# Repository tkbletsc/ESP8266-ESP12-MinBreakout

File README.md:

# ESP8266-ESP12-MinBreakout
Minimal breakout board for the ESP8266 model ESP12 board

A breakout board for the ESP8266 model ESP12 board, but with a twist. The down-facing header pins are installed with very little protrusion on the top, then some insulation is added (electrical tape), then the ESP12 is SMT soldered on top. This makes this breakout far smaller than the existing ones, and much more breadboard friendly.

Comes in through-hole and SMT flavors. The through-hole flavor rev1 has been successfully fabbed and populated and works perfectly.

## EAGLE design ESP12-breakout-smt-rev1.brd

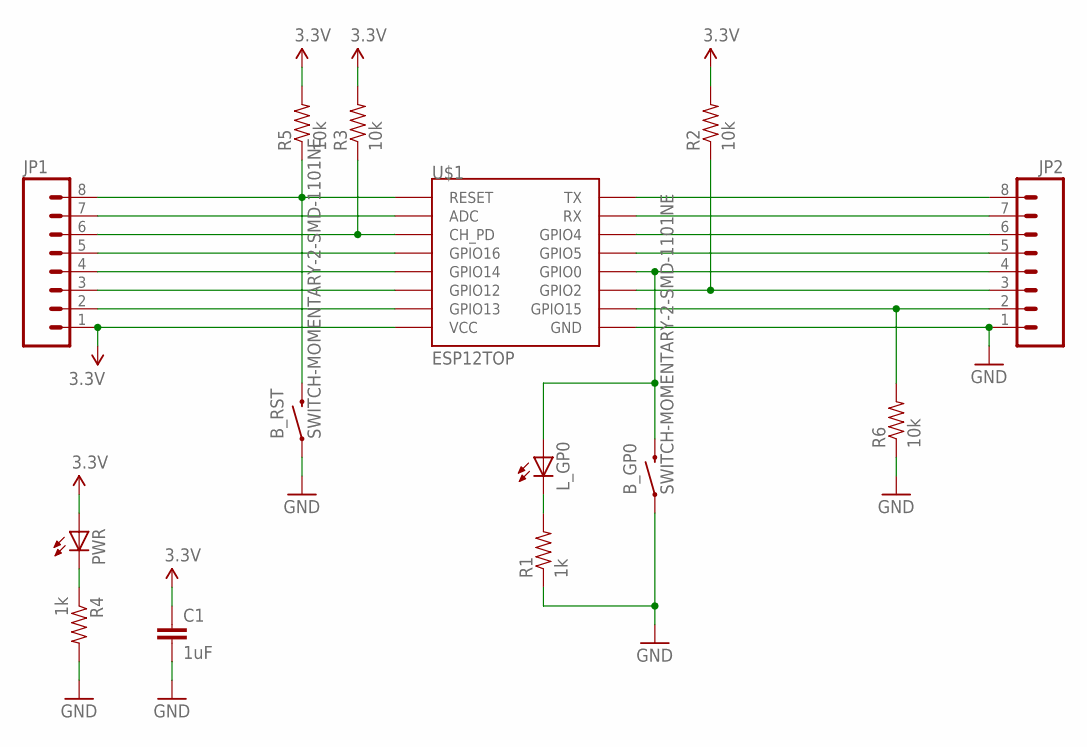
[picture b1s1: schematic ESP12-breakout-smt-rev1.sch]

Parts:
B_GP0: SWITCH-MOMENTARY-2-SMD-1101NE; TACTILE-SWITCH-1101NE
B_RST: SWITCH-MOMENTARY-2-SMD-1101NE; TACTILE-SWITCH-1101NE
C1: 1uF; 0805
JP1, JP2: M08; 1X08_PIN1_NO_SILK
L_GP0: LEDCHIPLED_0805; CHIPLED_0805
PWR: LEDCHIPLED_0805; CHIPLED_0805
R1, R4: 1k; 0603-RES
R2, R3, R5, R6: 10k; 0603-RES
U$1: ESP12TOP

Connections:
3.3V: C1.1, JP1.1, PWR.A, R2.2, R3.2, R5.2, U$1.VCC
GND: B_GP0.1, B_RST.1, C1.2, JP2.1, R1.1, R4.2, R6.1, U$1.GND
unnamed: L_GP0.C, R1.2
unnamed: JP1.2, U$1.GPIO13
unnamed: JP1.3, U$1.GPIO12
unnamed: JP1.4, U$1.GPIO14
unnamed: JP1.5, U$1.GPIO16
unnamed: JP1.6, R3.1, U$1.CH_PD
unnamed: JP1.7, U$1.ADC
unnamed: B_RST.2, JP1.8, R5.1, U$1.RESET
unnamed: PWR.C, R4.1
unnamed: JP2.2, R6.2, U$1.GPIO15
unnamed: JP2.3, R2.1, U$1.GPIO2
unnamed: B_GP0.2, JP2.4, L_GP0.A, U$1.GPIO0
unnamed: JP2.5, U$1.GPIO5
unnamed: JP2.6, U$1.GPIO4
unnamed: JP2.7, U$1.RXD (RX)
unnamed: JP2.8, U$1.TXD (TX)

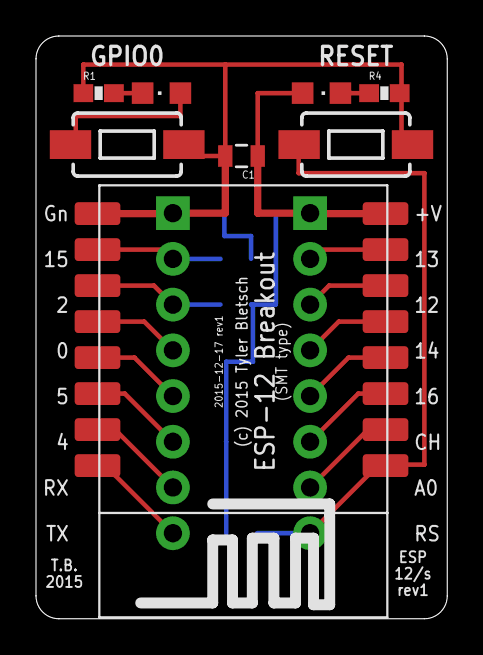
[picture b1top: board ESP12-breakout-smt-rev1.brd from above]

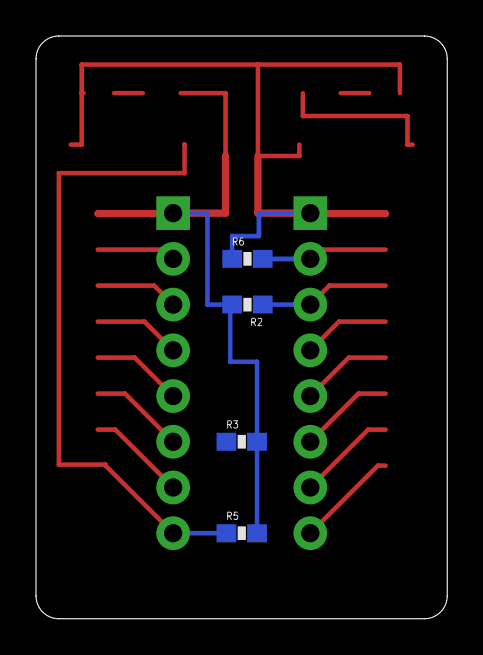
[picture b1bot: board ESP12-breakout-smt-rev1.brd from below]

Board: 2 copper layers, 22.8 x 32.4 mm, 14 parts (4 on the bottom side), 18 nets.

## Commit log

2016-02-12 :neckbeard: Added .gitattributes & .gitignore files

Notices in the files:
ESP12-breakout-smt-rev1.brd:
(c) 2015 Tyler Bletsch
parts and their libraries:
SparkFun-Resistors: Licensing: Creative Commons ShareAlike 4.0 International - https://creativecommons.org/licenses/by-sa/4.0
